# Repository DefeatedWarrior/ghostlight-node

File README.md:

<div align="center">

# 👻 Ghostlight Node

**A low-cost, open-source Art-Net / sACN → DMX512 node with PoE**

Two RDM-capable DMX ports · ESP32-S3 · W5500 Ethernet · 802.3af PoE · USB-C

-green)

[Docs](docs/) · [Wiki pages](wiki/Home.md) · [Ordering](docs/08-ordering-guide.md) · [Known issues](docs/11-known-issues-and-verification-status.md) · [Firmware](https://github.com/DefeatedWarrior/ghostlight-node-firmware)

</div>

| Front | Back (silkscreen only, mirrored) |
|---|---|
|  |  |

> **Status:** rev1 is design-complete but **has not been manufactured or tested**. Treat the first batch as a prototype run and read [known issues](docs/11-known-issues-and-verification-status.md) before ordering.

## Why

A *ghost light* is the single bulb left burning on an otherwise dark stage. The node does the same quiet job: it keeps the rig alive and listening while nothing else is on. The goal is a DMX node you can build for a small fraction of the cost of commercial units, with every file open.

## At a glance

| | |
|---|---|
| **Protocols** | Art-Net, sACN (E1.31), RDM |
| **DMX** | 2 bidirectional ports, SN65HVD72 (fail-safe for open/short/idle), TVS protected |
| **Per port** | IN and OUT 3-pole 5.08 mm terminals in parallel, 120 Ω jumper termination, GPIO-switchable bias |
| **MCU** | ESP32-S3-WROOM-1-N8 (8 MB flash, no PSRAM) |
| **Network** | WIZnet W5500, HR871150C PoE magjack, Wi-Fi also on module |
| **Power** | 802.3af PoE (SDAPO DP9700-5V, 5 V / 2 A), USB-C, or external 5 V |
| **I/O** | WS2812B status LED, LED per port, BOOT/RESET buttons, UART0 debug header |
| **Expansion** | 12-pin header J5 for a third port or other add-ons |
| **Board** | 100 × 100 mm, 2 layers, 1.6 mm, 4 × M3, hand-assembly friendly |

## Get started

1. **Order the PCB:** upload `fabrication/ghostlight-node-rev1-gerbers.zip` to JLCPCB (2 layers, 100 × 100 mm, 1.6 mm, HASL lead-free).
2. **Order parts:** import `bom/BOM_order_purchase.csv` into LCSC's BOM tool, scale for your board count, add about 10 % spare passives, check stock ([guide](docs/08-ordering-guide.md)).
3. **Assemble** by hand: [assembly guide](docs/09-assembly-guide.md).
4. **Bring up** in order (USB power, 3V3, Ethernet, DMX, then PoE): [test plan](docs/10-bring-up-and-test.md).
5. **Flash the firmware** from [ghostlight-node-firmware](https://github.com/DefeatedWarrior/ghostlight-node-firmware) with ESP-IDF 5.2.6: clone it, then run `tools/build.sh ghostlight-rev1 -p PORT flash monitor` ([firmware guide](https://github.com/DefeatedWarrior/ghostlight-node-firmware/blob/main/docs/DEVELOPING.md), [hardware notes](docs/13-firmware-integration.md)).

## Repository layout

| Path | Contents |
|---|---|
| `hardware/kicad/` | KiCad 7 project, `ESPNODE` symbol library and `ESPNODE.pretty` footprints |
| `fabrication/` | Gerber/drill zip for JLCPCB, individual gerbers, `pos.csv` |
| `bom/` | `BOM_order.csv` (per line, with designators), `BOM_order_purchase.csv` (LCSC part + quantity), `netlist.net` |
| `docs/` | Full documentation, schematic PDF, images |
| `wiki/` | Wiki pages (Home, FAQ, troubleshooting...) ready to publish to the GitHub wiki |
| `tools/generator/` | Python scripts that generated the board (reference only) |

## Documentation

| Build it | Understand it | Use it |
|---|---|---|
| [07 BOM and sourcing](docs/07-bom-and-sourcing.md) | [01 Overview and specs](docs/01-overview-and-specifications.md) | [13 Firmware integration](docs/13-firmware-integration.md) |
| [08 Ordering guide](docs/08-ordering-guide.md) | [02 Architecture and power](docs/02-architecture-and-power.md) | [05 DMX ports](docs/05-dmx-ports.md) |
| [09 Assembly guide](docs/09-assembly-guide.md) | [03 Pin map and connectors](docs/03-pinout-and-connectors.md) | [06 USB and debug](docs/06-usb-programming-debug.md) |
| [10 Bring-up and test](docs/10-bring-up-and-test.md) | [04 Ethernet and PoE](docs/04-ethernet-and-poe.md) | [11 Known issues](docs/11-known-issues-and-verification-status.md) |
| [14 Regenerating the design](docs/14-regenerating-the-design.md) | [12 PCB design notes](docs/12-pcb-design-notes.md) | [15 Roadmap / rev2](docs/15-roadmap.md) |

The schematic is in [docs/schematic.pdf](docs/schematic.pdf).

## Firmware

The firmware is in its own repository, [ghostlight-node-firmware](https://github.com/DefeatedWarrior/ghostlight-node-firmware): ESP-IDF, MIT, originally ESP-NODE-2RDM by ThinhCNTT22. It is not tied to this board. It has a board profile for rev1 (8 MB flash, no PSRAM, 8 MB partition table, port LEDs on GPIO5/6, DMX bias switches, W5500 reset), plus profiles for the N16R8 dev-board prototype and a plain ESP32 DevKitC, and other ESP32-S3 or ESP32 boards with RS485 transceivers can be added with one pin header and one settings file. Optional features (sACN, RDM, scenes, DMX tools, web log, mDNS, Ethernet) can be switched off at build time. The firmware builds with ESP-IDF 5.2.6 for this board (`tools/build.sh ghostlight-rev1`) with no warnings, and CI builds it on every change. **It has not been run on a Ghostlight board yet**; the same firmware runs on the N16R8 dev-board prototype. The firmware still calls itself `ESP-NODE-2RDM` in places. See its [DEVELOPING.md](https://github.com/DefeatedWarrior/ghostlight-node-firmware/blob/main/docs/DEVELOPING.md).

## Contributing

See [CONTRIBUTING.md](CONTRIBUTING.md). Results from a built board (photos, scope captures, what broke) are the most valuable contribution.

## Licence

Hardware files: **CERN-OHL-P-2.0** ([LICENSE](LICENSE)). Firmware: MIT ([ghostlight-node-firmware](https://github.com/DefeatedWarrior/ghostlight-node-firmware/blob/main/LICENSE)).

"Ghostlight Node" has not been trademark-cleared; check your own country's register before selling boards under it. Art-Net is a trademark of Artistic Licence Engineering Ltd; ESP32 of Espressif Systems; W5500 of WIZnet. Names are used only to describe compatibility.

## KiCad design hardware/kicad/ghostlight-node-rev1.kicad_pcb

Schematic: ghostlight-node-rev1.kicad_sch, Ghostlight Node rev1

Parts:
C1, C6, C14, C18: 10uF; C_0805_2012Metric
C2, C4, C10, C11, C12, C13, C15, C21, C30, C40: 100nF; C_0603_1608Metric
C3: 1uF; C_0603_1608Metric
C5, C50: 220uF; CP_Elec_6.3x5.4
C7: 22uF; C_0805_2012Metric
C16: 22nF; C_0603_1608Metric
C17: 4.7uF; C_0805_2012Metric
C19, C20: 18pF; C_0603_1608Metric
C23: 10nF; C_0603_1608Metric
D1, D2: SM712; SOT-23; LCSC C2943053
D3, D4, D5: SS14; D_SMA
D30: P1; LED_0603_1608Metric
D40: P2; LED_0603_1608Metric
F1: PTC 1.1A; Fuse_1206_3216Metric
H1, H2, H3, H4: M3; MountingHole_3.2mm_M3
J1: HR871150C; RJ45_Hanrun_HR871150C; LCSC C19724786
J2: DMX1; TerminalBlock_bornier-3_P5.08mm
J2O: DMX1_OUT; TerminalBlock_bornier-3_P5.08mm
J2T: TERM1; PinHeader_1x02_P2.54mm_Vertical
J3: DMX2; TerminalBlock_bornier-3_P5.08mm
J3O: DMX2_OUT; TerminalBlock_bornier-3_P5.08mm
J3T: TERM2; PinHeader_1x02_P2.54mm_Vertical
J4: USB-C (device/sink); USB_C_Receptacle_HRO_TYPE-C-31-M-12
J5: PORT3/EXPANSION; PinHeader_1x12_P2.54mm_Vertical
J6: 5V_EXT (PoE splitter / DC); PinHeader_1x02_P2.54mm_Vertical
J7: DEBUG UART0 (GND/TX/RX); PinHeader_1x03_P2.54mm_Vertical
L1: FB 120R@100MHz; L_0603_1608Metric
LED1: WS2812B; LED_WS2812B_PLCC4_5.0x5.0mm_P3.2mm
PS1: DP9700-5V; PoE_SDAPO_DP9700; LCSC C5380091
Q1, Q2: 2N7002; SOT-23
R1, R5, R8, R9, R10, R11, R30, R40: 10k; R_0603_1608Metric
R2: 330; R_0603_1608Metric
R3, R4: 5.1k; R_0603_1608Metric
R6: 12.4k 1%; R_0603_1608Metric
R7, R12: 1M; R_0603_1608Metric
R31, R32, R41, R42: 240 1%; R_0603_1608Metric
R33, R43: 100k; R_0603_1608Metric
R34, R44: 120 1%; R_0603_1608Metric
R35, R45: 1k; R_0603_1608Metric
R50, R51: 220; R_0603_1608Metric
SW1: BOOT; SW_SPST_TL3342
SW2: RESET; SW_SPST_TL3342
U1: ESP32-S3-WROOM-1-N8; ESP32-S3-WROOM-1; LCSC C2913202
U2: W5500; LQFP-48_7x7mm_P0.5mm; LCSC C32843
U3, U4: SN65HVD72DR; SOIC-8_3.9x4.9mm_P1.27mm; LCSC C48125
U5: AMS1117-3.3; SOT-223-3_TabPin2; LCSC C6186
U6: USBLC6-2SC6; SOT-23-6
Y1: 25MHz; Crystal_SMD_3225-4Pin_3.2x2.5mm

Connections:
5V_EXT: C50.1, D4.2 (A), J6.1, PS1.8
+3V3: C1.1, C2.1, C7.1, C15.1, C21.2, C30.1, C40.1, J5.1, L1.1, R1.1, R8.1, R9.1, R10.1, R11.1, R31.1, R41.1, R50.1, R51.1, U1.2 (3V3), U2.28 (VDD), U3.8 (VCC), U4.8 (VCC), U5.2 (VO)
+5V: C5.1, C6.1, D3.1 (K), D4.1 (K), D5.2 (A), J5.2, U5.3 (VI)
AVDD: C10.1, C11.1, C12.1, C13.1, C14.1, L1.2, U2.4 (AVDD), U2.8 (AVDD), U2.11 (AVDD), U2.15 (AVDD), U2.17 (AVDD), U2.21 (AVDD)
BIAS1: Q1.1 (G), R33.1, U1.39 (IO1)
BIAS1_N: Q1.3 (D), R32.2
BIAS2: Q2.1 (G), R43.1, U1.38 (IO2)
BIAS2_N: Q2.3 (D), R42.2
BIAS3: J5.7, U1.22 (IO14)
BOOT: SW1.1, U1.27 (IO0)
CC1: J4.A5 (CC1), R3.1
CC2: J4.B5 (CC2), R4.1
CHASSIS: C23.1, J1.SH (SHIELD), R12.1
DIR3: J5.6, R5.1, U1.23 (IO21)
DMX1_A: D1.1 (A1), J2.2, J2O.2, R31.2, R34.1, U3.6 (A)
DMX1_B: D1.2 (A2), J2.1, J2O.1, J2T.2, R32.1, U3.7 (B)
DMX1_DIR: R30.1, U1.32 (IO39), U3.2 (~RE), U3.3 (DE)
DMX1_RX: U1.9 (IO16), U3.1 (RO)
DMX1_TX: U1.10 (IO17), U3.4 (DI)
DMX2_A: D2.1 (A1), J3.2, J3O.2, R41.2, R44.1, U4.6 (A)
DMX2_B: D2.2 (A2), J3.1, J3O.1, J3T.2, R42.1, U4.7 (B)
DMX2_DIR: R40.1, U1.33 (IO40), U4.2 (~RE), U4.3 (DE)
DMX2_RX: U1.11 (IO18), U4.1 (RO)
DMX2_TX: U1.8 (IO15), U4.4 (DI)
EN: C3.1, R1.2, SW2.1, U1.3 (EN)
EXP1: J5.9, U1.31 (IO38)
EXP2: J5.10, U1.34 (IO41)
EXP3: J5.11, U1.35 (IO42)
EXP4: J5.12, U1.24 (IO47)
EXRES1: R6.1, U2.10 (EXRES1)
GND: C1.2, C2.2, C3.2, C4.2, C5.2, C6.2, C7.2, C10.2, C11.2, C12.2, C13.2, C14.2, C15.2, C16.2, C17.2, C18.2, C19.2, C20.2, C23.2, C30.2, C40.2, C50.2, D1.3 (common), D2.3 (common), D30.1 (K), D40.1 (K), J2.3, J2O.3, J3.3, J3O.3, J4.A1 (GND), J4.A12 (GND), J4.B1 (GND), J4.B12 (GND), J4.S1 (SHIELD), J5.3, J6.2, J7.1, LED1.3 (VSS), PS1.7, Q1.2 (S), Q2.2 (S), R3.2, R4.2, R5.2, R6.2, R12.2, R30.2, R33.2, R40.2, R43.2, SW1.2, SW2.2, U1.1 (GND), U1.40 (GND), U1.41 (GND), U2.3 (AGND), U2.9 (AGND), U2.14 (AGND), U2.16 (AGND), U2.19 (AGND), U2.29 (GND), U2.48 (AGND), U3.5 (GND), U4.5 (GND), U5.1 (GND), U6.2 (GND), Y1.2, Y1.4
JLED_ACT_A: J1.11 (LED_Y_A), R50.2
JLED_LNK_A: J1.13 (LED_G_A), R51.2
LEDK1: D30.2 (A), R35.2
LEDK2: D40.2 (A), R45.2
LED_ACT: J1.12 (LED_Y_K), U2.27 (ACTLED)
LED_DIN: LED1.4 (DIN), R2.2
LED_LINK: J1.14 (LED_G_K), U2.25 (LINKLED)
LED_P1: R35.1, U1.5 (IO5)
LED_P2: R45.1, U1.6 (IO6)
LED_P3: J5.8, U1.7 (IO7)
LED_STATUS: R2.1, U1.25 (IO48)
LED_VDD: C4.1, D5.1 (K), LED1.1 (VDD)
PMODE: R8.2, U2.43 (PMODE2), U2.44 (PMODE1), U2.45 (PMODE0)
POE_A1: J1.7 (VC1+), PS1.1
POE_A2: J1.8 (VC1-), PS1.2
POE_B1: J1.9 (VC2+), PS1.3
POE_B2: J1.10 (VC2-), PS1.4
RXN: J1.5 (RD-), U2.5 (RXN)
RXP: J1.4 (RD+), U2.6 (RXP)
TCT: C21.1, J1.3 (CT)
TERM1: J2T.1, R34.2
TERM2: J3T.1, R44.2
TOCAP: C17.1, U2.20 (TOCAP)
TXN: J1.2 (TD-), U2.1 (TXN)
TXP: J1.1 (TD+), U2.2 (TXP)
UART0_RX: J5.5, J7.3, U1.36 (RXD0)
UART0_TX: J5.4, J7.2, U1.37 (TXD0)
USB_DM: J4.A7 (D-), J4.B7 (D-), U1.13 (IO19), U6.3 (I/O2), U6.4 (I/O2)
USB_DP: J4.A6 (D+), J4.B6 (D+), U1.14 (IO20), U6.1 (I/O1), U6.6 (I/O1)
V1P2: C18.1, U2.22 (1V2O)
VBG: C16.1, U2.18 (VBG)
VBUS: F1.1, J4.A4 (VBUS), J4.A9 (VBUS), J4.B4 (VBUS), J4.B9 (VBUS), U6.5 (VBUS)
VBUS_F: D3.2 (A), F1.2
W5500_CS: R10.2, U1.18 (IO10), U2.32 (~SCS)
W5500_INT: R11.2, U1.17 (IO9), U2.36 (~INT)
W5500_MISO: U1.21 (IO13), U2.34 (MISO)
W5500_MOSI: U1.19 (IO11), U2.35 (MOSI)
W5500_RST: R9.2, U1.4 (IO4), U2.37 (~RST)
W5500_SCK: U1.20 (IO12), U2.33 (SCLK)
XI: C19.1, R7.1, U2.30 (XI/CLKIN), Y1.1
XO: C20.1, R7.2, U2.31 (XO), Y1.3

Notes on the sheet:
ESP32-S3 module, buttons, status LED, expansion and debug headers
USB-C (device/sink), power input OR-ing, 3.3 V regulator
Ethernet: W5500 + HR871150C PoE magjack (link/activity LEDs)
PoE: SDAPO DP9700-5V isolated 802.3af module (inputs from jack centre taps / spare pairs)
DMX port 1: RS-485 (SN65HVD72), TVS, bias switch, termination, IN/OUT terminals
DMX port 2: RS-485 (SN65HVD72), TVS, bias switch, termination, IN/OUT terminals
Mounting holes

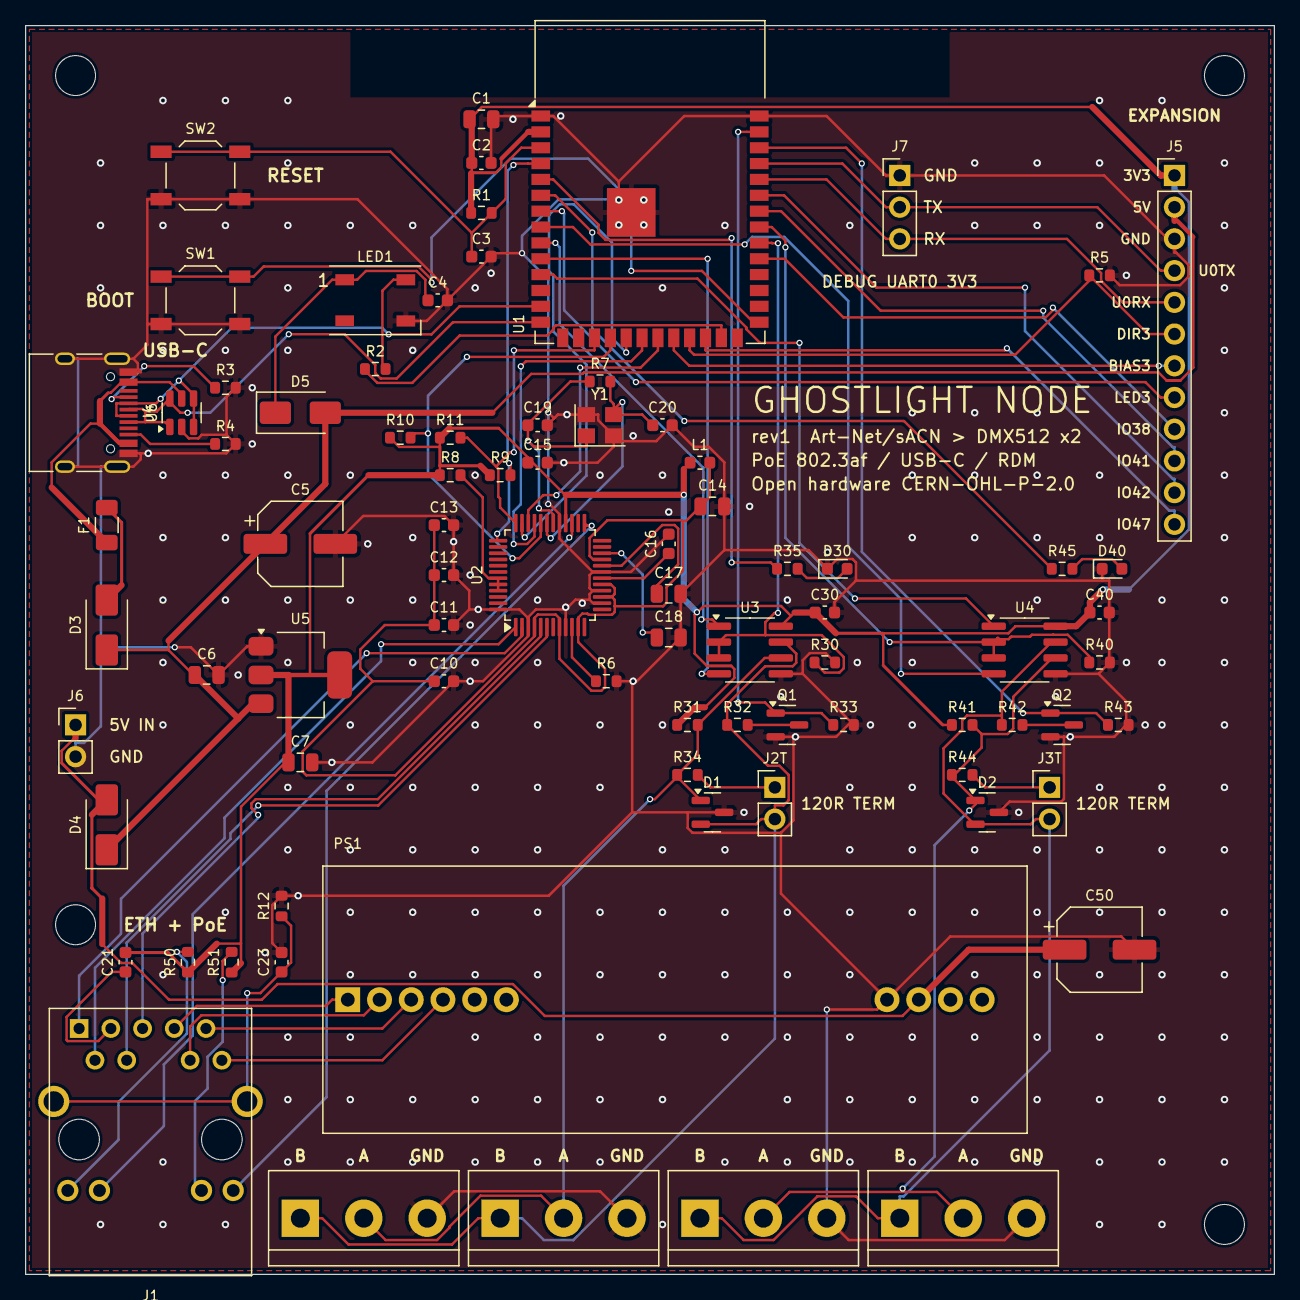
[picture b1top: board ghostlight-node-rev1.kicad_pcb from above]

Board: 2 copper layers, 100.0 x 100.0 mm, 86 parts (0 on the bottom side), 72 nets.

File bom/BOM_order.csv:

lcsc,refs,qty,value,footprint,part,status
C15850,C1 C6 C14 C18,4,10uF,C_0805_2012Metric,Samsung CL21A106KAYNNNE 10uF 0805,OK
C21122,C16,1,22nF,C_0603_1608Metric,Samsung CL10B223KB8NNNC 22nF,OK
C1779,C17,1,4.7uF,C_0805_2012Metric,Samsung CL21A475KAQNNNE 4.7uF 0805,OK
C107040,C19 C20,2,18pF,C_0603_1608Metric,Yageo CC0603JRNPO9BN180 18pF 50V NP0,OK
C1591,C2 C4 C10 C11 C12 C13 C15 C21 C30 C40,10,100nF,C_0603_1608Metric,Samsung CL10B104KB8NNNC 100nF 50V X7R,OK
C1589,C23,1,10nF,C_0603_1608Metric,Samsung CL10B103KB8NNNC 10nF,OK
C29936,C3,1,1uF,C_0603_1608Metric,Samsung CL10B105KA8NNNC 1uF 25V X7R 0603,OK
C32514,C5 C50,2,220uF,CP_Elec_6.3x5.4,Honor RVT0J221M0605 220uF 6.3V 6.3x5.4,OK
C45783,C7,1,22uF,C_0805_2012Metric,Samsung CL21A226MAQNNNE 22uF 0805,OK
C2943053,D1 D2,2,SM712,SOT-23,SM712 SOT-23 TVS,OK*
C12065,D30,1,P1,LED_0603_1608Metric,LITEON LTST-C193TGKT-5A emerald green 0603,OK
C12065,D40,1,P2,LED_0603_1608Metric,LITEON LTST-C193TGKT-5A emerald green 0603,OK
C2480,D5 D3 D4,3,SS14,D_SMA,MDD SS14 SMA,OK
C22366107,F1,1,PTC 1.1A,Fuse_1206_3216Metric,BORN SMD1206-110/6N PTC,OK
C19724786,J1,1,HR871150C,RJ45_Hanrun_HR871150C,Hanrun HR871150C 10/100 PoE RJ45 magjack,OK*
C474953,J2 J2O J3 J3O,4,Screw terminal 3P 5.08,TerminalBlock_bornier-3_P5.08mm,Cixi Kefa KF128-5.08-3P-AA screw terminal,OK
C165948,J4,1,USB-C (device/sink),USB_C_Receptacle_HRO_TYPE-C-31-M-12,HRO TYPE-C-31-M-12,OK
C2337,J5,1,PinHeader_1x12_P2.54mm_Vertical,PinHeader_1x12_P2.54mm_Vertical,BOOMELE 2.54mm 1x40P pin header (snap to length),OK
C2337,J6 J2T J3T,3,PinHeader_1x02_P2.54mm_Vertical,PinHeader_1x02_P2.54mm_Vertical,BOOMELE 2.54mm 1x40P pin header (snap to length),OK
C2337,J7,1,PinHeader_1x03_P2.54mm_Vertical,PinHeader_1x03_P2.54mm_Vertical,BOOMELE 2.54mm 1x40P pin header (snap to length),OK
C76892,L1,1,FB 120R@100MHz,L_0603_1608Metric,Murata BLM18AG121SN1D,OK
C114586,LED1,1,WS2812B,LED_WS2812B_PLCC4_5.0x5.0mm_P3.2mm,Worldsemi WS2812B-B/W 5050,OK
C5380091,PS1,1,DP9700-5V,PoE_SDAPO_DP9700,SDAPO DP9700-5V PoE PD module 5V/2A,OK*
C8545,Q1 Q2,2,2N7002,SOT-23,JSCJ 2N7002 SOT-23,OK
C25804,R1 R5 R8 R9 R10 R11 R30 R40,8,10k,R_0603_1608Metric,UNI-ROYAL 0603WAF1002T5E,OK
C23138,R2,1,330,R_0603_1608Metric,UNI-ROYAL 0603WAF3300T5E,OK
C23186,R3 R4,2,5.1k,R_0603_1608Metric,UNI-ROYAL 0603WAF5101T5E,OK
C23350,R31 R32 R41 R42,4,240 1%,R_0603_1608Metric,UNI-ROYAL 0603WAF2400T5E,OK
C25803,R33 R43,2,100k,R_0603_1608Metric,UNI-ROYAL 0603WAF1003T5E,OK
C22787,R34 R44,2,120 1%,R_0603_1608Metric,UNI-ROYAL 0603WAF1200T5E,OK
C21190,R35 R45,2,1k,R_0603_1608Metric,UNI-ROYAL 0603WAF1001T5E,OK
C22962,R50 R51,2,220,R_0603_1608Metric,UNI-ROYAL 0603WAF2200T5E,OK
C227572,R6,1,12.4k 1%,R_0603_1608Metric,Yageo AC0603FR-0712K4L 12.4k 1%,OK
C22935,R7 R12,2,1M,R_0603_1608Metric,UNI-ROYAL 0603WAF1004T5E,OK
C2886898,SW1,1,BOOT,SW_SPST_TL3342,E-Switch TL3342F160QG,OK
C2886898,SW2,1,RESET,SW_SPST_TL3342,E-Switch TL3342F160QG,OK
C2913198,U1,1,ESP32-S3-WROOM-1-N8,ESP32-S3-WROOM-1,Espressif ESP32-S3-WROOM-1-N8,OK*
C32843,U2,1,W5500,LQFP-48_7x7mm_P0.5mm,WIZnet W5500 LQFP-48,OK*
C48125,U3 U4,2,SN65HVD72DR,SOIC-8_3.9x4.9mm_P1.27mm,TI SN65HVD72DR,OK*
C6186,U5,1,AMS1117-3.3,SOT-223-3_TabPin2,AMS1117-3.3 SOT-223,OK*
C7519,U6,1,USBLC6-2SC6,SOT-23-6,ST USBLC6-2SC6,OK
C2842189,Y1,1,25MHz,Crystal_SMD_3225-4Pin_3.2x2.5mm,HCI XC32M4-25.000-F20NJDT 3225 25MHz 20pF,CHECK

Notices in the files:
hardware/kicad/ghostlight-node-rev1.kicad_pcb:
Open hardware (CERN-OHL-P-2.0)
CERN-OHL-P-2.0 open hardware
